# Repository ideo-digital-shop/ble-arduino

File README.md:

#Bluetooth Low-Energy Arduino Shield
*with the nBlue BLE Module, written by Jimmy Chion, IDEO*

license: [Creative Commons SA 3.0](http://creativecommons.org/licenses/by-sa/3.0/)

##Quick Start

On Arduino side:
Download and install the [Queuelist library for Arduino](http://playground.arduino.cc/Code/QueueList)
(to install, just drag and drop the QueueList folder into /Documents/Arduino/libraries/)

Download and install the BLEcontroller library.

Upload the sketch BLE_tester.ino onto your 3.3V Pro Mini. Open the Serial Monitor, 9600 Baudrate with Carriage Return.

On the iOS side:
go to the nBlue Forum and download the Sample Client (scroll to bottom of this doc to for site and login). Install it onto your BLE-enabled iOS device (much easier said than done).

Opening up Sample Client on your iOS device and scanning for devices should find the advertising BLE shield.
Connect to it, and you will see the blinking light turn solid. In Serial Monitor, you will see it spit out
information that it is now connected. You now have an open serial-like connection between the two.

##About

Bluetooth 4.0 is a great way to get information in and out of the iPhone 4s, iPad 3, and other new Apple products. It provides a quick wireless link for easy prototyping. 

This documentation probably has a missing sections. Please direct ANY AND ALL questions to

* Jimmy Chion(jchion@ideo.com) - firmware design
* Kyle Doerksen(kdoerksen@ideo.com) - hardware design
* Dan Goodwin(dg@ideo.com) - iOS layer (no longer with IDEO)

The product has since evolved from [IDEO Labs post](http://labs.ideo.com/2012/07/02/bluetooth-4-0-as-a-prototyping-tool/)

The shield is designed for Arduino Pro Mini and for Bluetooth 4.0 <-> iOS (bi-directional).

##Limitations

Bluetooth 4.0 (aka Bluetooth Low-Energy aka BLE) operates at the same frequency as classic BT, but has a much slower data rate of 200kb/s. It has a range of about 50-70m outdoors.

With our library, data rate is throttled down for accuracy. From BLE module to Arduino, we are limited by the Software Serial, which is kinda accurate at 19200 baud. (more about why we are using Software Serial instead of the TX/RX on the Arduino in the Hardware section of this doc).

##Pre-setup

The pre-setup was taken care of by IDEO Bay Area for the included boards. This section is for documentation purposes only.

The firmware on the nBlue BLE modules is often out of date and needs a firmware update for it to work with iOS.

To update the firmware, open up nBlueProg.exe and plug the module into an [FTDI usb plug](http://www.sparkfun.com/products/9873). Don't forget the board operates at 3.3V, so the FTDI has to be 3.3V. 

Here's the pin mapping from FTDI to module (or Arduino)
3v3 -- VCC
GND -- GND (both GNDs)
TX -- TX (yes, this is unconventional)
RX -- RX (currently pin 7)

See hardware > test rig for photos of Bay Area's setup

Make sure your Windows machine has [FTDI drivers](http://www.ftdichip.com/Drivers/VCP.htm) installed and recognizes the FTDI USB thing as a COM port. 

See embedded software > firmware update
Open up the nBlueProg.exe and point it to the correct .brx firmware update. You can download the [latest update](http://www.blueradios.com/forum/. (See Online section of this doc for log in info.)

After you have updated the firmware, leave it powered. The green light should be blinking to indicate it is in advertising mode. You can now open up the iPhone app, nBlue Sample Client. Click on Scan, and then the name of the advertising BLE module. The red LED on the module should now be solid.

We're now connected and paired with the module. We need to change the baud rate to 19200 (instead of 115200 default) in order for Software Serial to work. To do this, we click on the rightmost button which should say "Data." Clicking on that changes it to Command mode, which means we can talk to the BLE module through Bluetooth to send it AT commands. If the button now says Command, we are in Command mode.

Typing a simple `AT` should elicit an `OK`.

Type `ATSUART,4,0,0,1`. This changes the baudrate to 19200, 8, n, 1. See the ATSUART under the AT.s command set if you need to change the baudrate to anything else.

From there, we're good to go. At this point, if you open up any Serial Monitor from Arduino and set the baudrate to 19200, with Carriage Return, then you should be able to just type stuff into the Serial Monitor and see it appear on the iPhone app and vise versa. If it looks like gibberish, power cycle the arduino and check that it's `ATSUART?` gets a reply of `4,0,0,1`. Sometimes the changed setting doesn't stick.

Again, we took care of all this for you in the two modules included, but we're describing it here for when you produce your own boards.

##Setup from factory-reset modules

Here's setup for simple serial communication between BLE module and iPhone

Assumptions at this point:
* BLE module's firmware is up to date (1.2.1.3.1.0-S3.brx as of 02.01.13)
* baudrate for SoftwareSerial is correct (19200 for now). In other words, if you ran the command `ATSUART?`, you would get a reply of `4,0,0,1`.

1. get the nBlue Sample Client app loaded onto an iOS device with Bluetooth 4.0. This includes iPhone 4s, iPad 3, and the new MacBook Air and Pros.

2. stack the shield onto a Pro Mini. MAKE SURE IT'S 3.3V AND NOT 5V.

3. Open up nBlue_tester.ino and load it onto the Arduino.

4. Open the Serial Monitor, set baudrate to 9600 with line ending: Carriage Return

5. Open up the iPhone app and connect to the advertising BLE Module

6. Typing something into the Serial Monitor should show up on the iPhone App. Likewise, typing something into the app should show up in the Serial Monitor.

##Hardware

See hardware > schematics_nano_bluetooth4_3.3v for schematics

We're using SoftwareSerial to send data between the Arduino and BLE module. The BLE module then sends the info through Bluetooth to the iOS. The SoftwareSerial's tx/rx are IO pins 6 and 7 on the arduino.

The rest of the hardware is pretty simple. VCC and GND are connected and that's about it.

We've bridged CTS and DTR pins manually, but we'll put that in future versions.

##Arduino Library
To install library, add it to your Arduino's "libraries" folder and then write `#include "BLEcontroller.h"` to your sketch.

see embedded software > libraries

The library packages the AT.s commands into simple Arduino functions. This library still needs a lot of work and could be adapted for each specific application. For example, the RC car we built used a protocol that was modified. At some point, it would be nice to have insertable protocols.

Read through the .h file to get an understanding of the different functions. 

###Arduino Examples

BLE_tester.ino
shows off the possible functions exposed by the BLEcontroller library.

BLE_SerialExample.ino
Allows you to talk to the device without the use of BLEcontroller library. Refer to the AT commandset that nBlue publishes.
You can find that in the forum.

More specific information and comments inside each Arduino sketch.

##iOS 
(hasn't been updated since the IDEO labs post)

here's what Dan wrote:

For software questions (and I expect there to be a lot of them), 
ping Dan <dg@ideo.com>. 

Highlights of contents of iOS > our modified iPhone app:

NativeBridge.js 
is the code where the magic happens in terms of using javascript 
to call iOS code. This code was adopted from [this guy's blog](http://blog.techno-barje.fr/post/2010/10/06/UIWebView-secrets-part3-How-to-properly-call-ObjectiveC-from-Javascript/).

server.js 
is the master node file that returns the right interface, 
as well as doing some sweet real-time message passing with now.js

index.html 
is the first interface we made to steer the car. You can see the jquery+now.js
magic at the top of the file, and the NativeBridge.js code is at the bottom of the file

camera.html
is a quick and dirty copy of index.html, it is virtually identical,
albeit simplified to only send one control signal.

TO DO:

We did not have enough time to create an elegant message passing interface between the JS
and the iOS code. Right now we are running on a very simple protocol, the signals sent to
BT radio are in the form "(a,b,c,d)" where each letter is a number from 0-10. You can 
see how this is handled in the WebBridgeView.m file at the "steerCar" section in the
`- (void)handleCall:(NSString*)functionName callbackId:(int)callbackId args:(NSArray*)args`
function

##Online resources

* [nBlue forum](http://www.blueradios.com/forum/)

* nBlue AT.s Command Set
see forum above

* [FTDI drivers](http://www.ftdichip.com/Drivers/VCP.htm)

* [SoftwareSerial](http://arduino.cc/hu/Reference/SoftwareSerial)

* [a look at Apple's CoreBluetooth](http://developer.apple.com/library/ios/#samplecode/TemperatureSensor/Introduction/Intro.html)

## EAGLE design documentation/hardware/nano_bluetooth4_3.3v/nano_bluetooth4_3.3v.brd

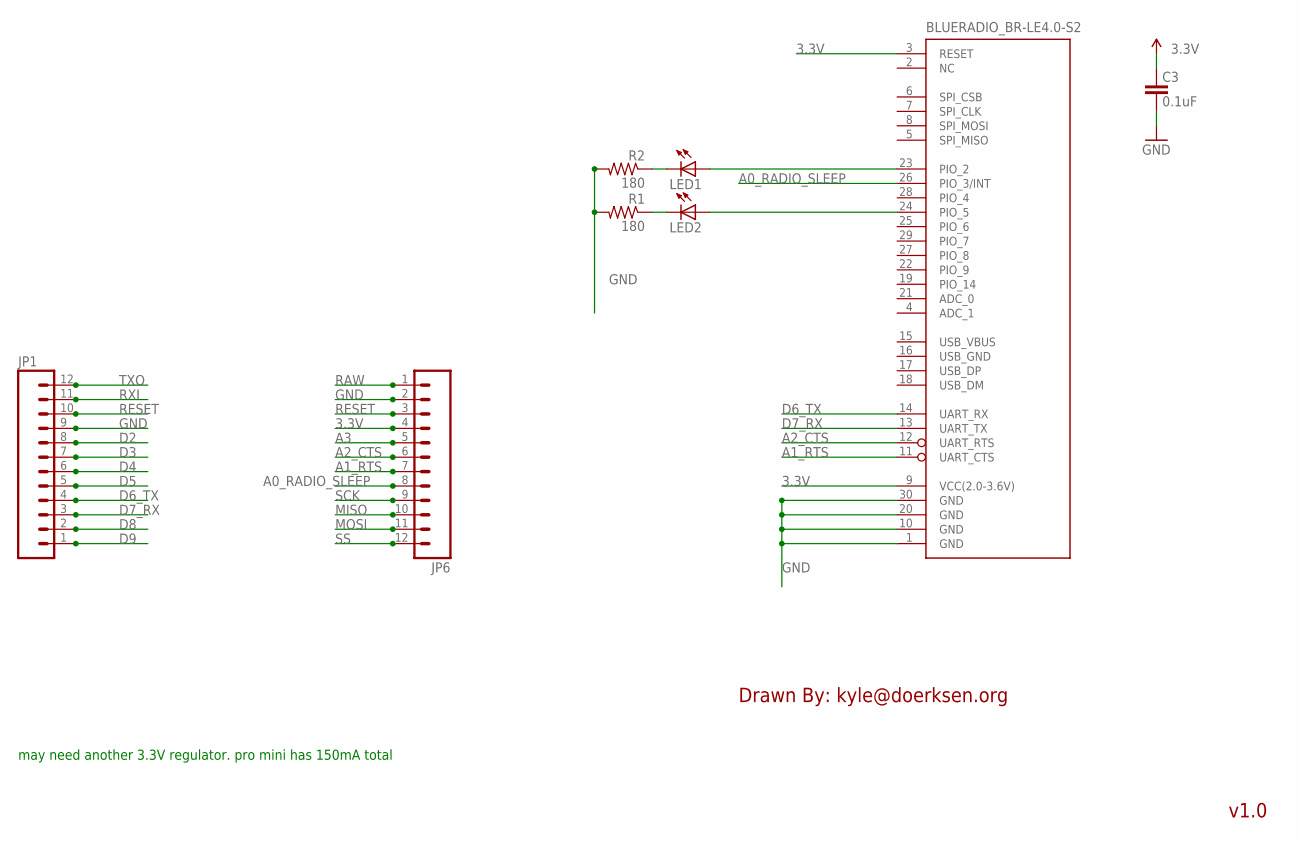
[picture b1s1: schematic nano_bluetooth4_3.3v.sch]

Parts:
BLUERADIO_BR-LE4.0-S2: BLUERADIO_BR-LE4.0-S2
C3: 0.1uF; 0402-CAP
JP1, JP6: M12PTH; 1X12
LED1, LED2: LED0603; LED-0603
R1, R2: 180; 0402-RES

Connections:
3.3V: BLUERADIO_BR-LE4.0-S2.3 (RESET), BLUERADIO_BR-LE4.0-S2.9 (VCC(2.0-3.6V)), C3.2, JP6.4
A0_RADIO_SLEEP: BLUERADIO_BR-LE4.0-S2.26 (PIO_3/INT), JP6.8
A1_RTS: BLUERADIO_BR-LE4.0-S2.11 (UART_CTS), JP6.7
A2_CTS: BLUERADIO_BR-LE4.0-S2.12 (UART_RTS), JP6.6
A3: JP6.5
D2: JP1.8
D3: JP1.7
D4: JP1.6
D5: JP1.5
D6_TX: BLUERADIO_BR-LE4.0-S2.14 (UART_RX), JP1.4
D7_RX: BLUERADIO_BR-LE4.0-S2.13 (UART_TX), JP1.3
D8: JP1.2
D9: JP1.1
GND: BLUERADIO_BR-LE4.0-S2.1 (GND), BLUERADIO_BR-LE4.0-S2.10 (GND), BLUERADIO_BR-LE4.0-S2.20 (GND), BLUERADIO_BR-LE4.0-S2.30 (GND), C3.1, JP1.9, JP6.2, R1.2, R2.2
MISO: JP6.10
MOSI: JP6.11
unnamed: BLUERADIO_BR-LE4.0-S2.24 (PIO_5), LED2.A
unnamed: LED1.C, R2.1
unnamed: BLUERADIO_BR-LE4.0-S2.23 (PIO_2), LED1.A
unnamed: LED2.C, R1.1
RAW: JP6.1
RESET: JP1.10, JP6.3
RXI: JP1.11
SCK: JP6.9
SS: JP6.12
TXO: JP1.12

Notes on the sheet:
may need another 3.3V regulator. pro mini has 150mA total
Drawn By: kyle@doerksen.org
v1.0

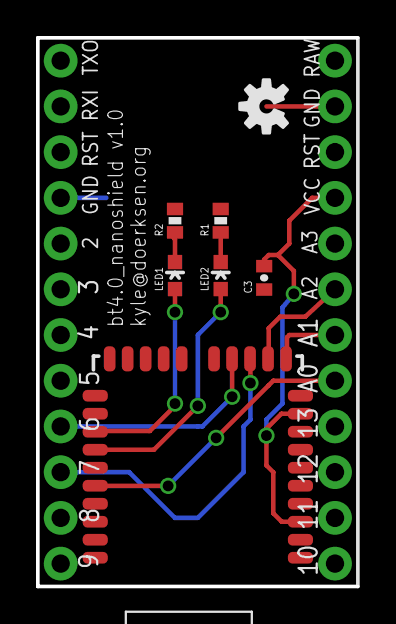
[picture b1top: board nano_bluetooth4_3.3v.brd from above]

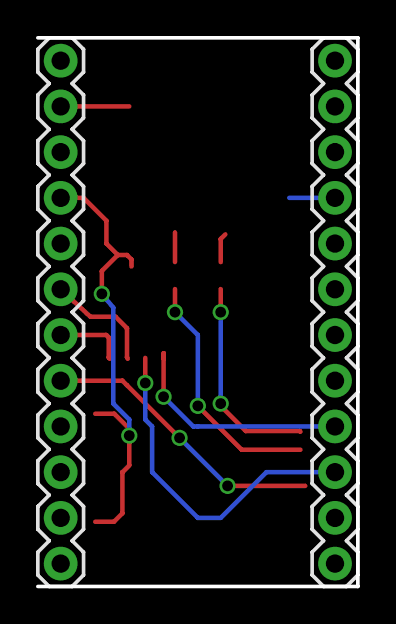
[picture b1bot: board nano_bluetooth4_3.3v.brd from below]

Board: 2 copper layers, 17.8 x 30.5 mm, 9 parts (2 on the bottom side), 12 nets.

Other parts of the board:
U$2: OSHW-LOGO-S

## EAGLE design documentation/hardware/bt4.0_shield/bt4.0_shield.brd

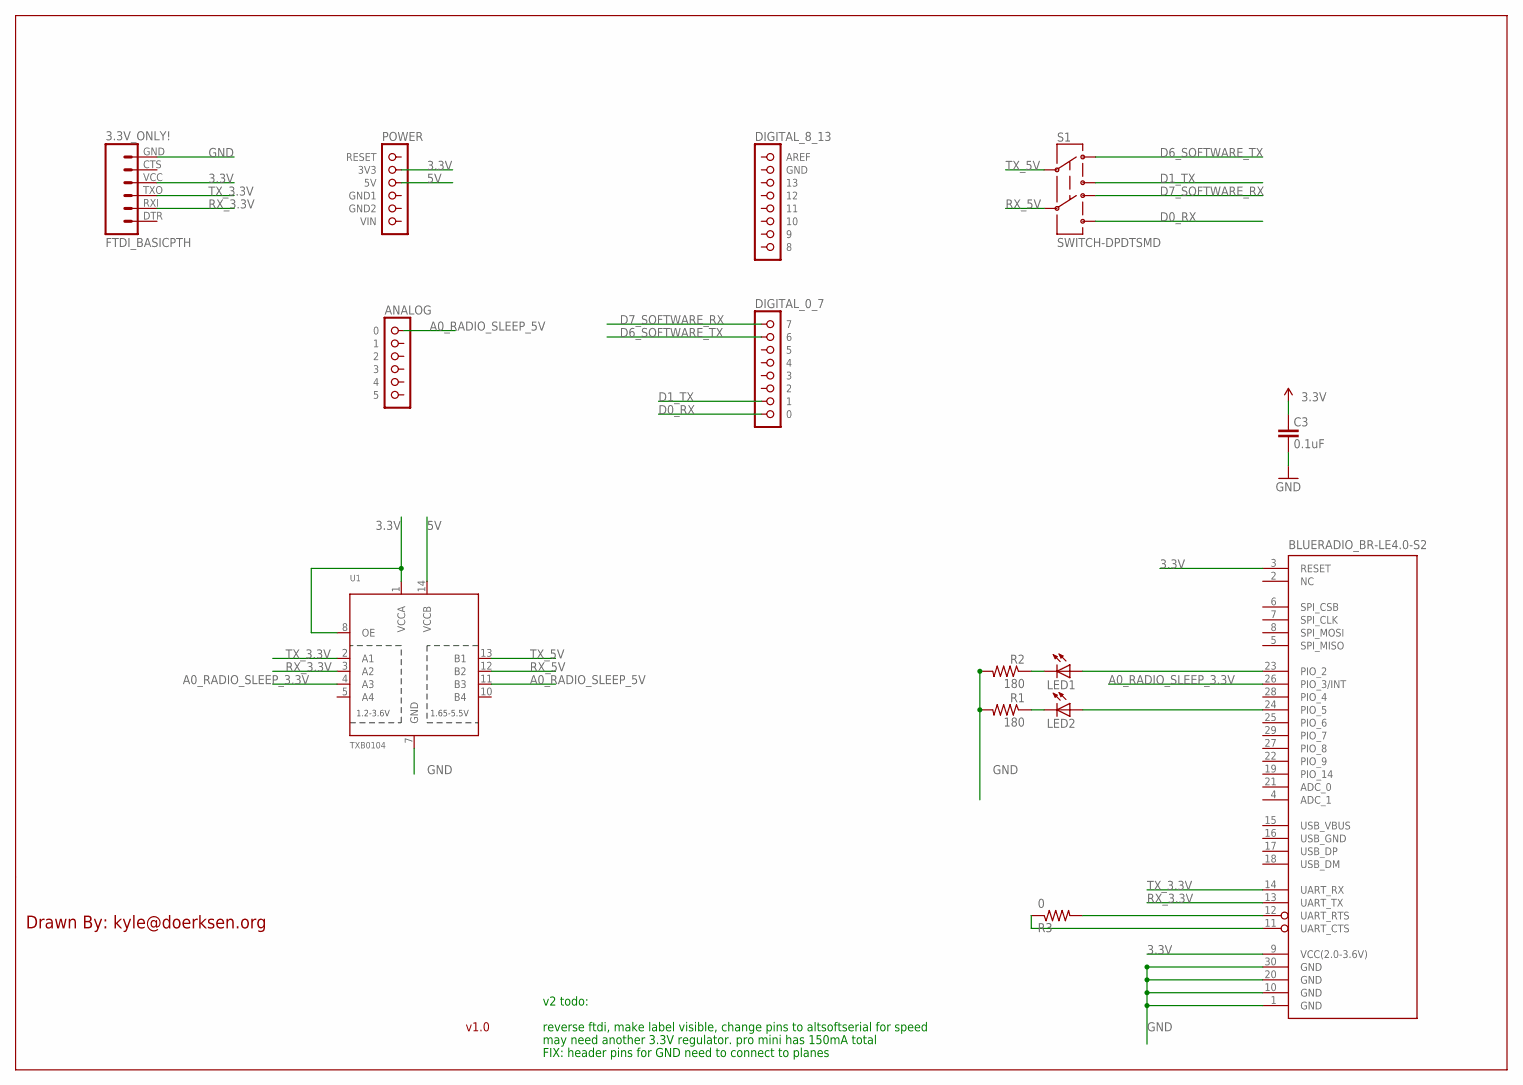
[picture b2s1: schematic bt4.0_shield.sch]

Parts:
3.3V_ONLY!: FTDI_BASICPTH; FTDI_BASIC
BLUERADIO_BR-LE4.0-S2: BLUERADIO_BR-LE4.0-S2
C3: 0.1uF; 0402-CAP
LED1, LED2: LED0603; LED-0603
R1, R2: 180; 0402-RES
R3: 0; 0402-RES
S1: SWITCH-DPDTSMD; AYZ0202
U1: TXB0104; SO14
U$1: POWER; 1X06
U$2: ANALOG; 1X06
U$3: DIGITAL_0_7; 1X08
U$4: DIGITAL_8_13; 1X08

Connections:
3.3V: 3.3V_ONLY!.VCC (4), BLUERADIO_BR-LE4.0-S2.3 (RESET), BLUERADIO_BR-LE4.0-S2.9 (VCC(2.0-3.6V)), C3.2, U1.1 (VCCA), U1.8 (OE), U$1.2 (3V3)
5V: U1.14 (VCCB), U$1.3 (5V)
A0_RADIO_SLEEP_3.3V: BLUERADIO_BR-LE4.0-S2.26 (PIO_3/INT), U1.4 (A3)
A0_RADIO_SLEEP_5V: U1.11 (B3), U$2.1 (0)
D0_RX: S1.6, U$3.8 (0)
D1_TX: S1.3, U$3.7 (1)
D6_SOFTWARE_TX: S1.1, U$3.2 (6)
D7_SOFTWARE_RX: S1.4, U$3.1 (7)
GND: 3.3V_ONLY!.GND (6), BLUERADIO_BR-LE4.0-S2.1 (GND), BLUERADIO_BR-LE4.0-S2.10 (GND), BLUERADIO_BR-LE4.0-S2.20 (GND), BLUERADIO_BR-LE4.0-S2.30 (GND), C3.1, R1.2, R2.2, U1.7 (GND)
unnamed: BLUERADIO_BR-LE4.0-S2.24 (PIO_5), LED2.A
unnamed: LED1.C, R2.1
unnamed: BLUERADIO_BR-LE4.0-S2.23 (PIO_2), LED1.A
unnamed: LED2.C, R1.1
unnamed: BLUERADIO_BR-LE4.0-S2.12 (UART_RTS), R3.2
unnamed: BLUERADIO_BR-LE4.0-S2.11 (UART_CTS), R3.1
RX_3.3V: 3.3V_ONLY!.RXI (2), BLUERADIO_BR-LE4.0-S2.13 (UART_TX), U1.3 (A2)
RX_5V: S1.5, U1.12 (B2)
TX_3.3V: 3.3V_ONLY!.TXO (3), BLUERADIO_BR-LE4.0-S2.14 (UART_RX), U1.2 (A1)
TX_5V: S1.2, U1.13 (B1)

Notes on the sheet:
may need another 3.3V regulator. pro mini has 150mA total
v2 todo:
reverse ftdi, make label visible, change pins to altsoftserial for speed
FIX: header pins for GND need to connect to planes
Drawn By: kyle@doerksen.org
v1.0

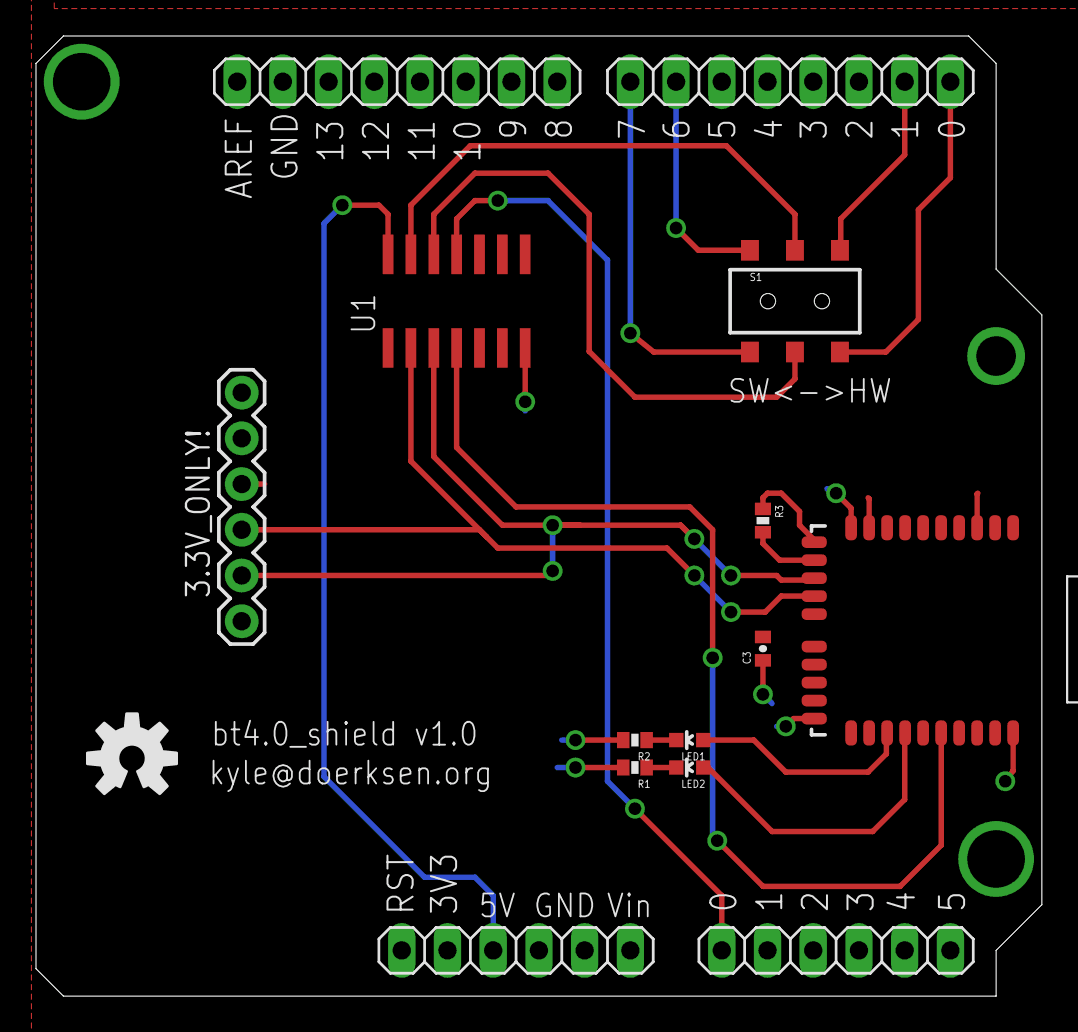
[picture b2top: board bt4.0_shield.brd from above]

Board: 2 copper layers, 55.9 x 53.3 mm, 15 parts (0 on the bottom side), 19 nets.

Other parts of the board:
U$7: OSHW-LOGO-M

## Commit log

2013-02-06 edit
2013-02-11 added license
2013-02-12 removed ignore files
2013-02-12 small edit
2013-02-12 added keywords.txt

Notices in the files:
parts and their libraries:
SparkFun-RF: Licensing: CC v3.0 Share-Alike You are welcome to use this library for commercial purposes.
